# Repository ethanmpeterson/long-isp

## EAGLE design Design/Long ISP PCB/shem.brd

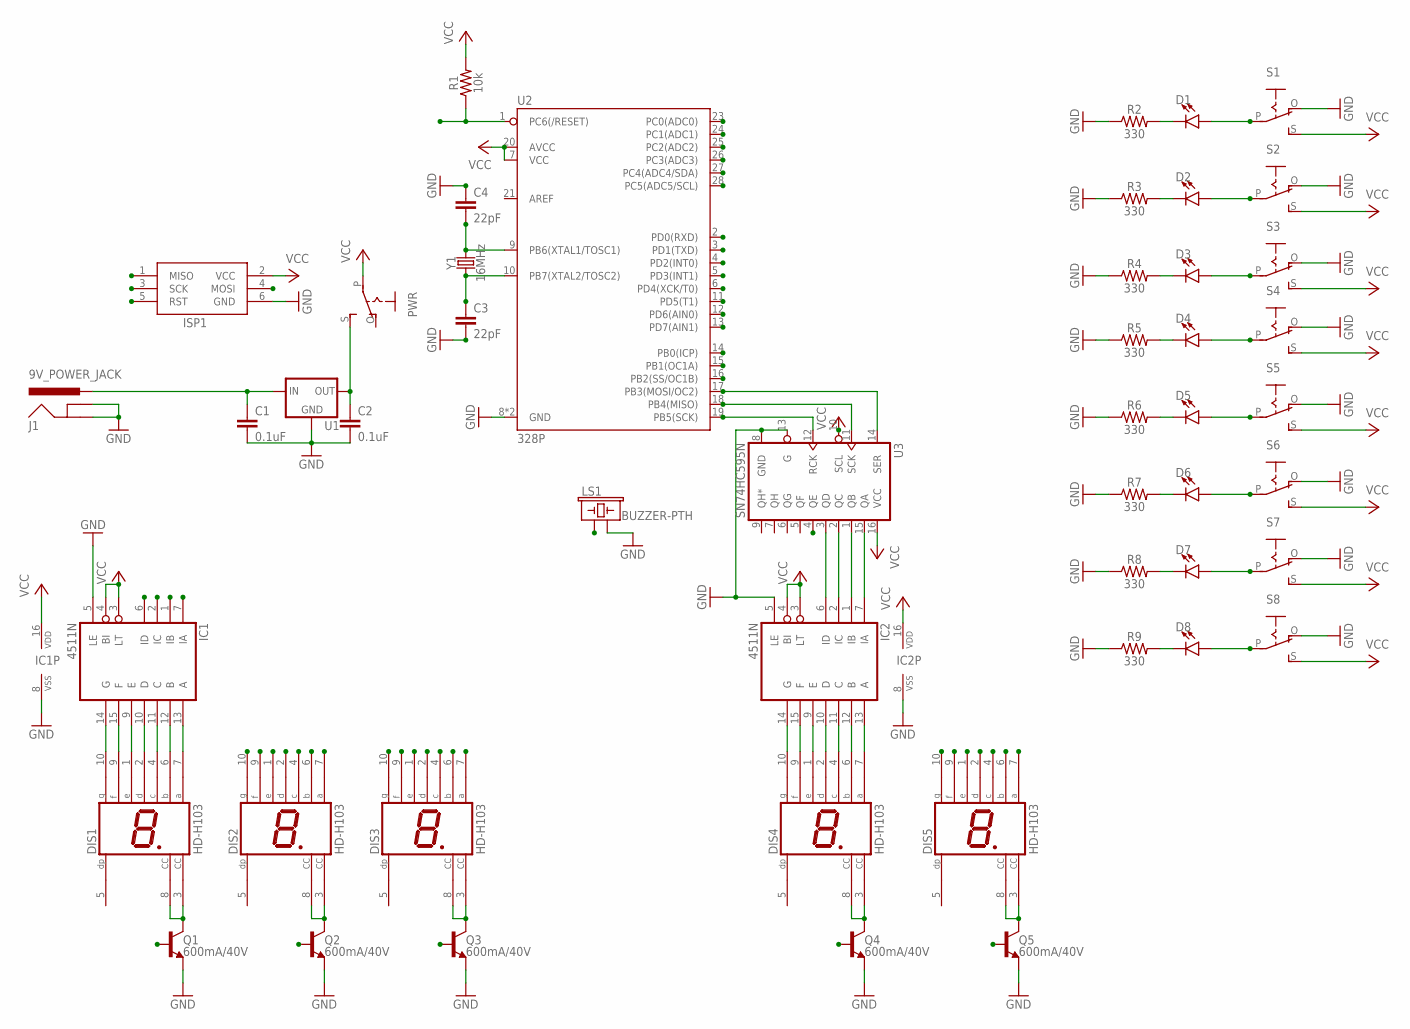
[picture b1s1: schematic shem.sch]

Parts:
C1, C2: 0.1uF; CAP-PTH-SMALL-KIT
C3, C4: 22pF; CAP-PTH-2.54
D1, D2, D3, D4, D5, D6, D7, D8: LED3MM; LED_3MM
DIS1, DIS2, DIS3, DIS4, DIS5: HD-H103; HDSP-M
IC1, IC2: 4511N; DIL16
ISP1: AVRISP-6; AVRISP
J1: 9V_POWER_JACK; POWER_JACK_PTH
LS1: BUZZER-PTH; BUZZER-12MM
PWR: EG1218S; EG1218
Q1, Q2, Q3, Q4, Q5: 600mA/40V; TO-92
R1: 10k; AXIAL-0.3
R2, R3, R4, R5, R6, R7, R8, R9: 330; AXIAL-0.3
S1, S2, S3, S4, S5, S6, S7, S8: EG1218S; EG1218
U1: V_REG_78XXSIDE; 78XXL
U2: 328P; DIP28
U3: SN74HC595N; DIP16
Y1: 16MHz; HC49US

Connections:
9V: C1.1, J1.PWR, U1.IN
BUZZ: LS1.+ (1), U3.4 (QE)
GND: C1.2, C2.2, C3.2, C4.1, IC1.5 (LE), IC1.8 (VSS), IC2.5 (LE), IC2.8 (VSS), ISP1.6 (GND), J1.GND, J1.GNDBREAK, LS1.- (2), Q1.3 (E), Q2.3 (E), Q3.3 (E), Q4.3 (E), Q5.3 (E), R2.P$1 (1), R3.P$1 (1), R4.P$1 (1), R5.P$1 (1), R6.P$1 (1), R7.P$1 (1), R8.P$1 (1), R9.P$1 (1), S1.O, S2.O, S3.O, S4.O, S5.O, S6.O, S7.O, S8.O, U1.GND, U2.8 (GND), U2.22 (GND), U3.8 (GND), U3.13 (G)
HUNDREDS_ENABLE: Q1.2 (B), U2.16 (PB2(SS/OC1B))
IA: IC1.7 (IA), U2.23 (PC0(ADC0))
IB: IC1.1 (IB), U2.24 (PC1(ADC1))
IC: IC1.2 (IC), U2.25 (PC2(ADC2))
ID: IC1.6 (ID), U2.26 (PC3(ADC3))
MISO: ISP1.1 (MISO), U2.18 (PB4(MISO)), U3.11 (SCK)
MOSI: ISP1.4 (MOSI), U2.17 (PB3(MOSI/OC2)), U3.14 (SER)
unnamed: C2.1, PWR.S, U1.OUT
unnamed: C3.1, U2.10 (PB7(XTAL2/TOSC2)), Y1.1
unnamed: C4.2, U2.9 (PB6(XTAL1/TOSC1)), Y1.2
unnamed: DIS1.3 (CC), DIS1.8 (CC), Q1.1 (C)
unnamed: IC2.7 (IA), U3.15 (QA)
unnamed: DIS2.3 (CC), DIS2.8 (CC), Q2.1 (C)
unnamed: IC2.1 (IB), U3.1 (QB)
unnamed: DIS3.3 (CC), DIS3.8 (CC), Q3.1 (C)
unnamed: IC2.2 (IC), U3.2 (QC)
unnamed: IC2.6 (ID), U3.3 (QD)
unnamed: DIS4.3 (CC), DIS4.8 (CC), Q4.1 (C)
unnamed: D1.K (C), R2.P$2 (2)
unnamed: D8.K (C), R9.P$2 (2)
unnamed: D7.K (C), R8.P$2 (2)
unnamed: D6.K (C), R7.P$2 (2)
unnamed: DIS5.3 (CC), DIS5.8 (CC), Q5.1 (C)
unnamed: D5.K (C), R6.P$2 (2)
unnamed: D4.K (C), R5.P$2 (2)
unnamed: D3.K (C), R4.P$2 (2)
unnamed: D2.K (C), R3.P$2 (2)
NUM_A: DIS1.7 (A), DIS2.7 (A), DIS3.7 (A), IC1.13 (A)
NUM_B: DIS1.6 (B), DIS2.6 (B), DIS3.6 (B), IC1.12 (B)
NUM_C: DIS1.4 (C), DIS2.4 (C), DIS3.4 (C), IC1.11 (C)
NUM_D: DIS1.2 (D), DIS2.2 (D), DIS3.2 (D), IC1.10 (D)
NUM_E: DIS1.1 (E), DIS2.1 (E), DIS3.1 (E), IC1.9 (E)
NUM_F: DIS1.9 (F), DIS2.9 (F), DIS3.9 (F), IC1.15 (F)
NUM_G: DIS1.10 (G), DIS2.10 (G), DIS3.10 (G), IC1.14 (G)
ONES_ENABLE: Q3.2 (B), U2.14 (PB0(ICP))
RST: ISP1.5 (RST), R1.P$1 (1), U2.1 (PC6(/RESET))
S0: D1.A, S1.P, U2.2 (PD0(RXD))
S1: D2.A, S2.P, U2.3 (PD1(TXD))
S2: D3.A, S3.P, U2.4 (PD2(INT0))
S3: D4.A, S4.P, U2.5 (PD3(INT1))
S4: D5.A, S5.P, U2.6 (PD4(XCK/T0))
S5: D6.A, S6.P, U2.11 (PD5(T1))
S6: D7.A, S7.P, U2.12 (PD6(AIN0))
S7: D8.A, S8.P, U2.13 (PD7(AIN1))
SCK: ISP1.3 (SCK), U2.19 (PB5(SCK)), U3.12 (RCK)
SCORE_A: DIS4.7 (A), DIS5.7 (A), IC2.13 (A)
SCORE_B: DIS4.6 (B), DIS5.6 (B), IC2.12 (B)
SCORE_C: DIS4.4 (C), DIS5.4 (C), IC2.11 (C)
SCORE_D: DIS4.2 (D), DIS5.2 (D), IC2.10 (D)
SCORE_E: DIS4.1 (E), DIS5.1 (E), IC2.9 (E)
SCORE_F: DIS4.9 (F), DIS5.9 (F), IC2.15 (F)
SCORE_G: DIS4.10 (G), DIS5.10 (G), IC2.14 (G)
SCORE_ONES_ENABLE: Q4.2 (B), U2.28 (PC5(ADC5/SCL))
SCORE_TENS_ENABLE: Q5.2 (B), U2.27 (PC4(ADC4/SDA))
TENS_ENABLE: Q2.2 (B), U2.15 (PB1(OC1A))
VCC: IC1.3 (LT), IC1.4 (BI), IC1.16 (VDD), IC2.3 (LT), IC2.4 (BI), IC2.16 (VDD), ISP1.2 (VCC), PWR.P, R1.P$2 (2), S1.S, S2.S, S3.S, S4.S, S5.S, S6.S, S7.S, S8.S, U2.7 (VCC), U2.20 (AVCC), U3.10 (SCL), U3.16 (VCC)

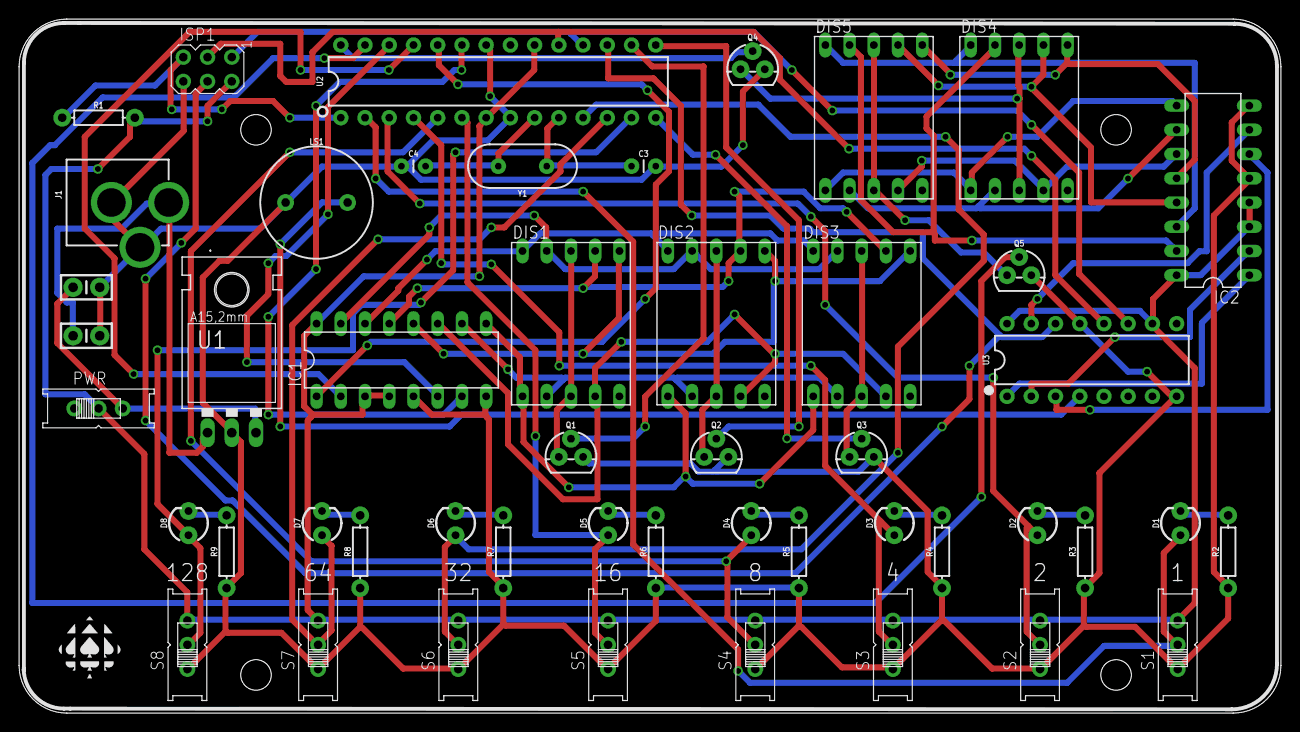
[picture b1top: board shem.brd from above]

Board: 2 copper layers, 132.3 x 72.8 mm, 49 parts (0 on the bottom side), 59 nets.

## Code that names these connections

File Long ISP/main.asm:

;
; Long ISP.asm
;
; Created: 2018-03-21 3:32:54 PM
; Author : Ethan Peterson
;

.cseg                                          ;load into Program Memory
#include "prescalers.h"
.org   0x0000                          ;start of Interrupt Vector (Jump) Table
        rjmp    reset                           ;address  of start of code
.equ size = 15
.org 0x000E
	rjmp TIM2_COMPA
.org 0x002A
	rjmp ADC_Complete
.org 0x0020
		rjmp TIM0_OVF

.org 0x001A
		rjmp TIM1_OVF

.org    0x100                                   ;abitrary address for start of code
 reset:
	clr r22
    ldi             r16, low(RAMEND)        ; ALL assembly code should start by
    out             spl,r16                 ; setting the Stack Pointer to
    ldi             r16, high(RAMEND)       ; the end of SRAM to support
    out             sph,r16                 ; function calls, etc.
   movw    z,x

.def original = r16 ; value to be pushed through double dabble algorithm
.def onesTens = r17 ; register holding ones and tens output nibbles from double dabble
.def hundreds = r22 ; hundreds output from double dabble
.def working = r24 ; register used to work with data that needs to be preserved elsewhere
.def addReg = r20 ; holds a value of 3 to be added to other registers in the double dabble process
.def times = r25 ; register holding the number of bit shifts the double dabble algorithm must do before being complete
.def input = r21 ; raw graycode input from rotary encoder
.def newValue = r23 ; where newly generated random numbers will be stored
.def score = r15
.def copy = r14
.def overflows = r13
.def gameEndFlag = r11
.def scoreCopy = r10

.equ data = PB3
.equ latch = PB5
.equ clk = PB4

rjmp setup

timers:
	//cli ; global interrupt disable
	ldi r16, T2ps1024 ; set the prescaler
	sts TCCR2B, r16 ; store to appropriate register
	ldi r16, 0x02 ; set timer mode 2
	sts TCCR2A, r16 ; store
	ldi r16, 124 ; set output compare number to get 63hz freq
	sts OCR2A, r16 ; store to output compare reg

	ldi r16, 1 << OCIE2A ; set timer interrupt enable bit
	sts TIMSK2, r16 ; enable the interrupt
	ret

ADCInit:
	ser r16 ; set all bits in r16
	ldi r16, (1 << REFS0) | (1 << ADLAR)
	sts ADMUX, r16
	; Enable, start dummy conversion, enable timer as trigger, prescaler
	ldi r16, (1 << ADEN) | (1 << ADSC) | (1 << ADIE) | (1 << ADPS2) | (1 << ADPS1) | (1 << ADPS0)
	sts ADCSRA, r16
	ldi r16, 1 << ADTS2
	sts ADCSRB, r16
dummy:
	lds r16, ADCSRA
	andi r16,  1 << ADIF
	breq dummy
	ret

ADC_Complete:
	lds newValue, ADCH ; grab ADC reading and place in gp reg
	reti

T0Init: ; initialize T0 interrupt to schedule ADC conversions
	clr r16
	out TCCR0A, r16 ; normal mode OC0A/B disconnected
	ldi r16, T0ps8 ; 
	out TCCR0B, r16
	ldi r16, 1 << TOIE0 ; Timer interrupt enable
	sts TIMSK0, r16 ; output to mask register to
	ret

T1Init: ; 1 Hz Timer overflow interrupt to monitor how long game has ran
	clr r16
	ldi r16, 1 << CS12
	sts TCCR1B, r16
	ldi r16, 1 << TOIE1
	sts TIMSK1, r16
	ret

TIM0_OVF:
	lds r19, ADCSRA ; start an ADC conversion
	sbr r19, 1 << ADSC ; set the required bit
	sts ADCSRA, r19
	reti

TIM1_OVF:
	dec overflows
	tst overflows
	breq fourMin
	reti

fourMin:
	; end the game here
	dec gameEndFlag
	reti

setup:
	
	ldi r16, 240
	mov overflows, r16
	ldi r16, 1
	mov gameEndFlag, r16

	clr newValue
	clr input
	clr copy
	clr original
	clr score
	cli

	rcall initScoreDisplay
	rcall initShiftReg
	rcall timers
	rcall ADCInit
	//rcall T0Init
	rcall T1Init
	sei
	rjmp loop

start:
	out 0x0A, hundreds ; clear DDRD register using 0 value in hundreds reg

	mov r17, newValue ; copy the seed
	and r17, r18 
	ldi r18, 0x43
	; generate random # in newValue reg using ADC reading as seed... reference: https://www.avrfreaks.net/forum/i-need-pseudo-random-number-generator-attiny-13
	lsr r17
	adc r18, r19
	lsr r17
	adc r18, r19
	lsr r17
	lsr r17
	lsr r17
	lsr r17
	lsr r17
	adc r18, r19
	bst r18, 0 ;
	bld newValue, 7
	lsr newValue

	mov original, newValue
	mov copy, newValue
	ret


.MACRO shiftOut ; MSBFIRST Shiftout
	cbi PORTB, latch
	; handle shifting data
	cbi PORTB, clk
	cbi PORTB, data
	sbrc @0, 7 ; skip if bit in register passed to macro is cleared
	sbi PORTB, data
	sbi PORTB, clk

	cbi PORTB, clk
	cbi PORTB, data
	sbrc @0, 6 ; skip if bit in register passed to macro is cleared
	sbi PORTB, data
	sbi PORTB, clk

	cbi PORTB, clk
	cbi PORTB, data
	sbrc @0, 5 ; skip if bit in register passed to macro is cleared
	sbi PORTB, data
	sbi PORTB, clk

	cbi PORTB, clk
	cbi PORTB, data
	sbrc @0, 4 ; skip if bit in register passed to macro is cleared
	sbi PORTB, data
	sbi PORTB, clk

	cbi PORTB, clk
	cbi PORTB, data
	sbrc @0, 3 ; skip if bit in register passed to macro is cleared
	sbi PORTB, data
	sbi PORTB, clk

	cbi PORTB, clk
	cbi PORTB, data
	sbrc @0, 2 ; skip if bit in register passed to macro is cleared
	sbi PORTB, data
	sbi PORTB, clk

	cbi PORTB, clk
	cbi PORTB, data
	sbrc @0, 1 ; skip if bit in register passed to macro is cleared
	sbi PORTB, data
	sbi PORTB, clk

	cbi PORTB, clk
	cbi PORTB, data
	sbrc @0, 0 ; skip if bit in register passed to macro is cleared
	sbi PORTB, data
	sbi PORTB, clk

	sbi PORTB, latch
.ENDMACRO

.MACRO doubleDabble
	ldi addReg, 3
	ldi times, 8
	clr onesTens
	clr hundreds
decideStep:
; check if 3 needs to be added to any of the ones tens or hundreds nibbles
checkOnes:
	mov working, onesTens
	andi working, 0b00001111 ; analyze only the lower nibble where ones value is
	cpi working, 5
	brsh addThreeOnes
checkTens:
	mov working, onesTens
	andi working, 0b11110000 ; analyze only the upper nibble where tens value is stored
	cpi working, 80
	brsh addThreeTens
checkHundreds:
	cpi hundreds, 5
	brsh addThreeHundreds
; bit shift
shift:
	lsl @0
	rol onesTens
	rol hundreds
	dec times
	cpi times, 0 ; if the @0 value has been shifted 8 times move to POV section of the code
	breq endDabble
	rjmp decideStep ; otherwise repeat

addThreeOnes:
	add onesTens, addReg
	rjmp checkTens

addThreeTens:
	swap onesTens
	add onesTens, addReg
	swap onesTens
	rjmp checkHundreds

addThreeHundreds:
	add hundreds, addReg
	rjmp shift
endDabble:
	//ret
.ENDMACRO

.MACRO numDisplaySelect ; MACRO to enable display of choice in number display
	cbi PORTB, PB2
	cbi PORTB, PB1
	cbi PORTB, PB0

	sbi PORTB, @0
.ENDMACRO

.MACRO scoreDisplaySelect ; MACRO to enable appropiate score display ones or tens
	cbi PORTC, PC4
	cbi PORTC, PC5

	sbi PORTC, @0
.ENDMACRO

.MACRO numDisplayOut
	cbi PORTC, PC0
	sbrc @0, 0
	sbi PORTC, PC0
	
	cbi PORTC, PC1
	sbrc @0, 1
	sbi PORTC, PC1
	
	cbi PORTC, PC2
	sbrc @0, 2
	sbi PORTC, PC2

	cbi PORTC, PC3
	sbrc @0, 3
	sbi PORTC, PC3
	
.ENDMACRO

display:
	rcall initNumDisplay ; set all transistor manipulation pins to output
	numDisplaySelect PB2
	numDisplayOut hundreds ; display hundreds
	rcall delay
	; switch to tens display
	numDisplaySelect PB1
	mov working, onesTens
	andi working, 0b11110000
	swap working
	numDisplayOut working
	rcall delay
	; switch to ones Display
	numDisplaySelect PB0
	mov working, onesTens
	andi working, 0b00001111
	numDisplayOut working
	rcall delay ; admire
	ret ;

scoreDisplay:
	scoreDisplaySelect PC5 ; select ones display
	mov r18, score ; retain score value
	doubleDabble r18
	mov working, onesTens
	andi working, 0b00001111
	shiftOut working
	rcall delay
	scoreDisplaySelect PC4 ; select tens display
	mov working, onesTens
	andi working, 0b11110000
	swap working
	shiftOut working
	mov r18, copy
	doubleDabble r18
	ret

delay: ; 1 ms delay
ldi  r18, 11
    ldi  r19, 99
L1: dec  r19
    brne L1
    dec  r18
    brne L1
	ret


loop:
	rcall display ; display POV for challenge number and score
	rcall scoreDisplay

	tst gameEndFlag
	breq gameEnd

	rjmp loop


gameEnd:
	ldi original, 0
	doubleDabble original
	rcall display
	mov scoreCopy, score
	doubleDabble scoreCopy
	rcall scoreDisplay
	rjmp gameEnd

TIM2_COMPA:
	in input, PIND
	cp input, copy
	breq isEqual
	reti

isEqual:
	inc score
	rcall start
	doubleDabble original
	reti

initShiftReg:
	sbi DDRB, PB3
	sbi DDRB, PB4
	sbi DDRB, PB5
	ldi original, 0
	shiftOut original
	ret

initScoreDisplay:
	sbi DDRC, PC4
	sbi DDRC, PC5
	ret

initNumDisplay:
	sbi DDRB, PB0
	sbi DDRB, PB1
	sbi DDRB, PB2

	sbi DDRC, PC0
	sbi DDRC, PC1
	sbi DDRC, PC2
	sbi DDRC, PC3
	ret

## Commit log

2018-03-21 created project and added baseline double dabble algorithm POV code
2018-03-21 added timer interrupt which will be used to check if the user successfully entered the correct switch combination
2018-03-21 revised ISR to handle switch input from PORTD TX and RX pins are problematic so another port may have to be used
2018-03-23 began restructuring code so I can use rcall in one main loop to get the same results
2018-03-26 value on displays now mirrors the value entered in binary via the switches
2018-03-28 game component now semi working incrimenting the number that you need to match by one in absence of working array or RNG
2018-03-28 game is now playable reading values from the table. unexplained initial value of 192 appearing despite not being entered into startTable
2018-03-28 moved code to double dabble label
2018-03-28 converted double dabble label to a re useable macro for other future uses
2018-04-02 successfully implemented shiftout macro
2018-04-02 started on label for displaying the score using a shift register connected to a 4511 and POV
2018-04-02 began re working display label to integrate with POV requirements of the score display
2018-04-02 added new macros to rework display label
2018-04-02 score display now working with some flicker issues
2018-04-02 fixed flicker issue
2018-05-26 commit to save progress
2018-05-26 added new array to populate with random numbers
2018-05-27 got random number gen up and running using ADC readings as the seed
2018-05-27 modified original random algorithm to produce better values with seeds from the delay registers r18 and r19
2018-05-27 cleaned up code and fixed swapped ones tens on score displays
2018-06-08 added an additional timer interrupt to handle the games start and end
2018-06-08 left score displayed at the end of the game
2018-06-10 set timing to four minutes
2018-06-10 added design folder with all cad work related to the binary game console
2018-06-10 staged the files
2018-06-10 added master power switch
2018-06-10 added 3mm leds to input switching
2018-06-11 fixed board schematic consistency sync issue as a result leds for input switches have been removed again
2018-06-11 re added led indicators to inputswitches
2018-06-11 laid out new components and autorouted the board
2018-06-11 signed my name and added ACES logo
2018-06-11 added white outline around the board on the silkscreen
2018-06-14 added gerber files and the CAM job used

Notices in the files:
parts and their libraries:
SparkFun-Connectors: Licensing: Creative Commons ShareAlike 4.0 International - https://creativecommons.org/licenses/by-sa/4.0
